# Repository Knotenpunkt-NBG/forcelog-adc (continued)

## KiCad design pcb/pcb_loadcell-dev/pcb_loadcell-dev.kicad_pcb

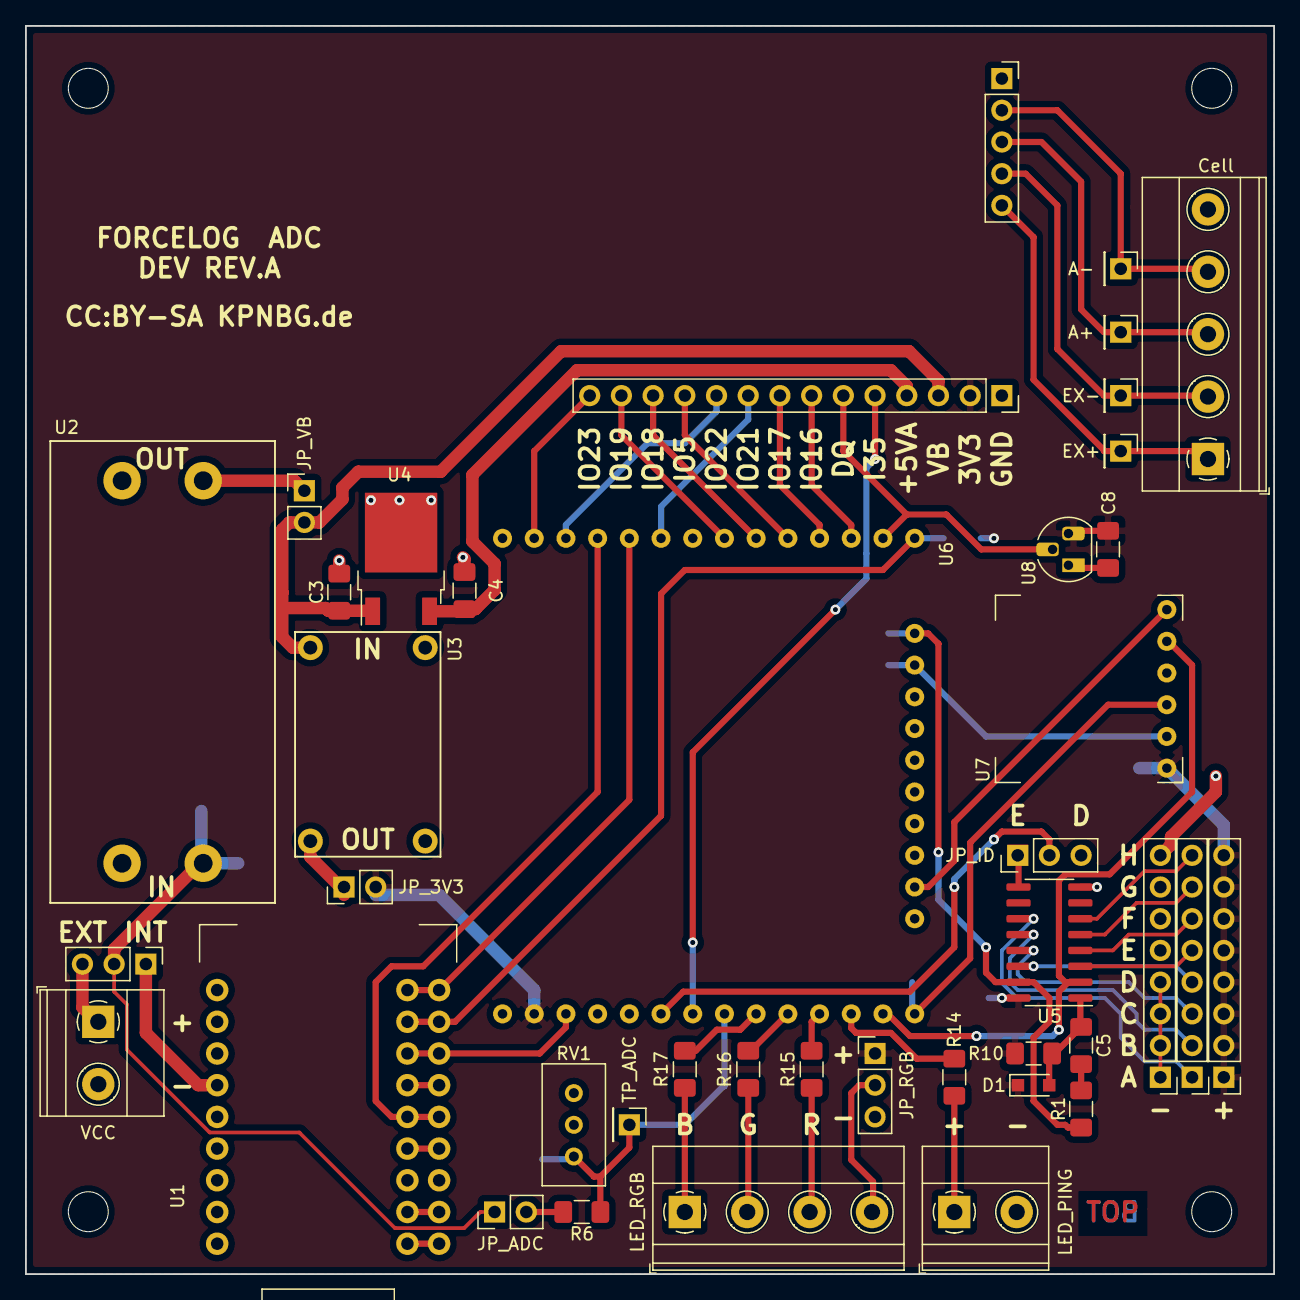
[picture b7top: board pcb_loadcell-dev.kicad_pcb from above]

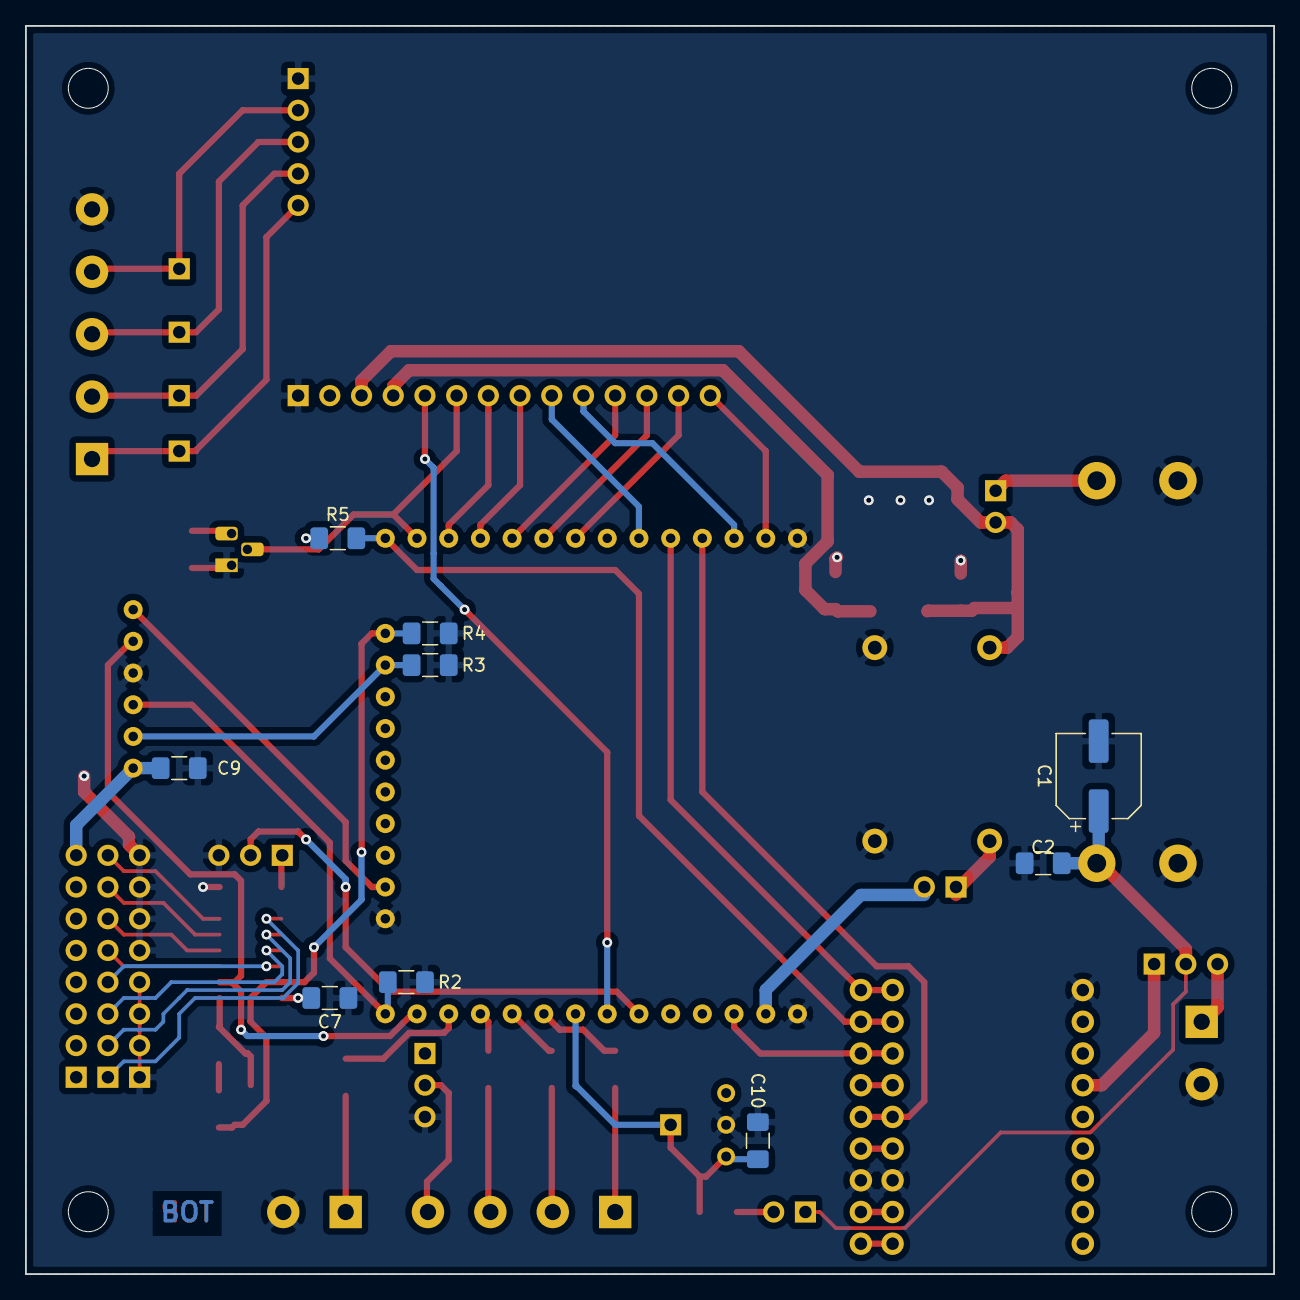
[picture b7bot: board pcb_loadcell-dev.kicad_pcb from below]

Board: 2 copper layers, 100.0 x 100.0 mm, 54 parts (9 on the bottom side), 55 nets.

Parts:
C1: 10µ; CP_Elec_6.3x4.9
C2, C4, C5, C7, C8, C9, C10: 100n; C_1206_3216Metric_Pad1.42x1.75mm_HandSolder
C3: 330n; C_1206_3216Metric_Pad1.42x1.75mm_HandSolder
D1: BAT54; D_SOD-323_HandSoldering
JP1: JUMPER3; PinHeader_1x03_P2.54mm_Vertical
JP2: JP_3V3; PinHeader_1x02_P2.54mm_Vertical
JP3: JP_ID; PinHeader_1x03_P2.54mm_Vertical
JP4: JP_VB; PinHeader_1x02_P2.54mm_Vertical
JP6: JP_ADC; PinHeader_1x02_P2.54mm_Vertical
JP8: JP_RGB; PinHeader_1x03_P2.54mm_Vertical
P1: VCC; TerminalBlock_Phoenix_MKDS-1,5-2_1x02_P5.00mm_Horizontal
P2, P3, P4: CONN_01X08; PinHeader_1x08_P2.54mm_Vertical
P5: CONN_01X14; PinSocket_1x14_P2.54mm_Vertical
P6, P7, P9, P15: CONN_01X01; MountingHole_3.2mm_M3
P8: TP_ADC; PinHeader_1x01_P2.54mm_Vertical
P10: LED_PING; TerminalBlock_Phoenix_MKDS-1,5-2_1x02_P5.00mm_Horizontal
P11: LED_RGB; TerminalBlock_Phoenix_MKDS-1,5-4_1x04_P5.00mm_Horizontal
P12: A-; PinHeader_1x01_P2.54mm_Vertical
P13: A+; PinHeader_1x01_P2.54mm_Vertical
P14: Cell; TerminalBlock_Phoenix_MKDS-1,5-5_1x05_P5.00mm_Horizontal
P16: CONN_01X05; PinSocket_1x05_P2.54mm_Vertical
P17: EX-; PinHeader_1x01_P2.54mm_Vertical
P18: EX+; PinHeader_1x01_P2.54mm_Vertical
R1, R10: 470; R_1206_3216Metric_Pad1.42x1.75mm_HandSolder
R2, R3, R4, R5: 10k; R_1206_3216Metric_Pad1.42x1.75mm_HandSolder
R6: 1k; R_1206_3216Metric_Pad1.42x1.75mm_HandSolder
R14, R17: 22; R_1206_3216Metric_Pad1.42x1.75mm_HandSolder
R15: 120; R_1206_3216Metric_Pad1.42x1.75mm_HandSolder
R16: 86; R_1206_3216Metric_Pad1.42x1.75mm_HandSolder
RV1: 1k; Potentiometer_Bourns_3296W_Vertical
U1: FT232breakout; ft232rl_breakout_combined
U2: BoostConverter; MT3608_module_boost
U3: BuckConverter; dsn-mini-360_buck
U4: 7805; TO-252-2
U5: 74HC165; SOIC-16_3.9x9.9mm_P1.27mm
U6: ESP32-WROOM-32U; ESP32-WROOM-BREAKOUT
U7: W25Q128; W25Q128-module
U8: DS18B20; TO-92_HandSolder

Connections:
+3V3: C7.1, C8.1, C9.1, D1.K, JP2.2, JP8.1, P2.1, P2.2, P2.3, P2.4, P2.5, P2.6, P2.7, P2.8, P5.2, R5.2, R10.1, U5.16, U6.2, U7.1, U8.3
+5VA: C4.1, P5.4, U4.3
/Digital/BLUE: R17.1, U6.9
/Digital/DQ: P5.6, U6.26, U8.2
/Digital/DTR: R5.1, U1.8, U6.25
/Digital/GREEN: R16.1, U6.10
/Digital/HCLK: U5.2, U6.13, U7.5
/Digital/HMISO: R2.1, U6.14, U7.3
/Digital/HMOSI: U6.16, U7.6
/Digital/H~CS: R3.1, U6.23, U7.2
/Digital/I35: P5.5, U6.7
/Digital/IO_5|V~CS: P5.11, U6.29
/Digital/IO_16: P5.7, U6.27
/Digital/IO_17: P5.8, U6.28
/Digital/IO_18|VCLK: P5.12, U6.30
/Digital/IO_19|VMISO: P5.13, U6.31
/Digital/IO_21|SDA: P5.9, U6.33
/Digital/IO_22|SCL: P5.10, U6.36
/Digital/IO_23|VMOSI: P5.14, U6.37
/Digital/PING: R14.2, U6.12
/Digital/QH: JP3.2, U6.6
/Digital/RED: R15.1, U6.11
/Digital/RTS: U1.7, U6.3
/Digital/RXD: U1.9, U6.34
/Digital/SH: R1.1, R4.2, U5.15, U6.24
/Digital/TXD: U1.5, U6.35
GND: C1.2, C2.2, C3.2, C4.2, C7.2, C8.2, C9.2, C10.2, JP3.3, JP8.3, P1.2, P3.1, P3.2, P3.3, P3.4, P3.5, P3.6, P3.7, P3.8, P5.1, P10.2, P14.5, P16.1, R2.2, R3.2, R4.1, RV1.2, U1.3, U1.18, U2.1, U2.4, U3.2, U3.4, U4.2, U5.8, U6.1, U6.15, U6.38, U7.4, U8.1
unnamed: C5.1, D1.A, R10.2, U5.1
unnamed: C5.2, R1.2
unnamed: C10.1, P8.1, R6.1, RV1.1, U6.8
unnamed: JP1.1, U1.15
unnamed: JP1.3, P1.1
unnamed: JP2.1, U3.3
unnamed: JP3.1, U5.9
unnamed: JP4.1, U2.3
unnamed: JP6.2, R6.2
unnamed: JP8.2, P11.4
unnamed: P4.1, U5.11
unnamed: P4.2, U5.12
unnamed: P4.3, U5.13
unnamed: P4.4, U5.14
unnamed: P4.5, U5.3
unnamed: P4.6, U5.4
unnamed: P4.7, U5.5
unnamed: P4.8, U5.6
unnamed: P10.1, R14.1
unnamed: P11.1, R17.2
unnamed: P11.2, R16.2
unnamed: P11.3, R15.2
unnamed: P12.1, P14.4, P16.2
unnamed: P13.1, P14.3, P16.3
unnamed: P14.1, P16.5, P18.1
unnamed: P14.2, P16.4, P17.1
VCC: C1.1, C2.1, JP1.2, JP6.1, U2.2
Vboost: C3.1, JP4.2, P5.3, U3.1, U4.1

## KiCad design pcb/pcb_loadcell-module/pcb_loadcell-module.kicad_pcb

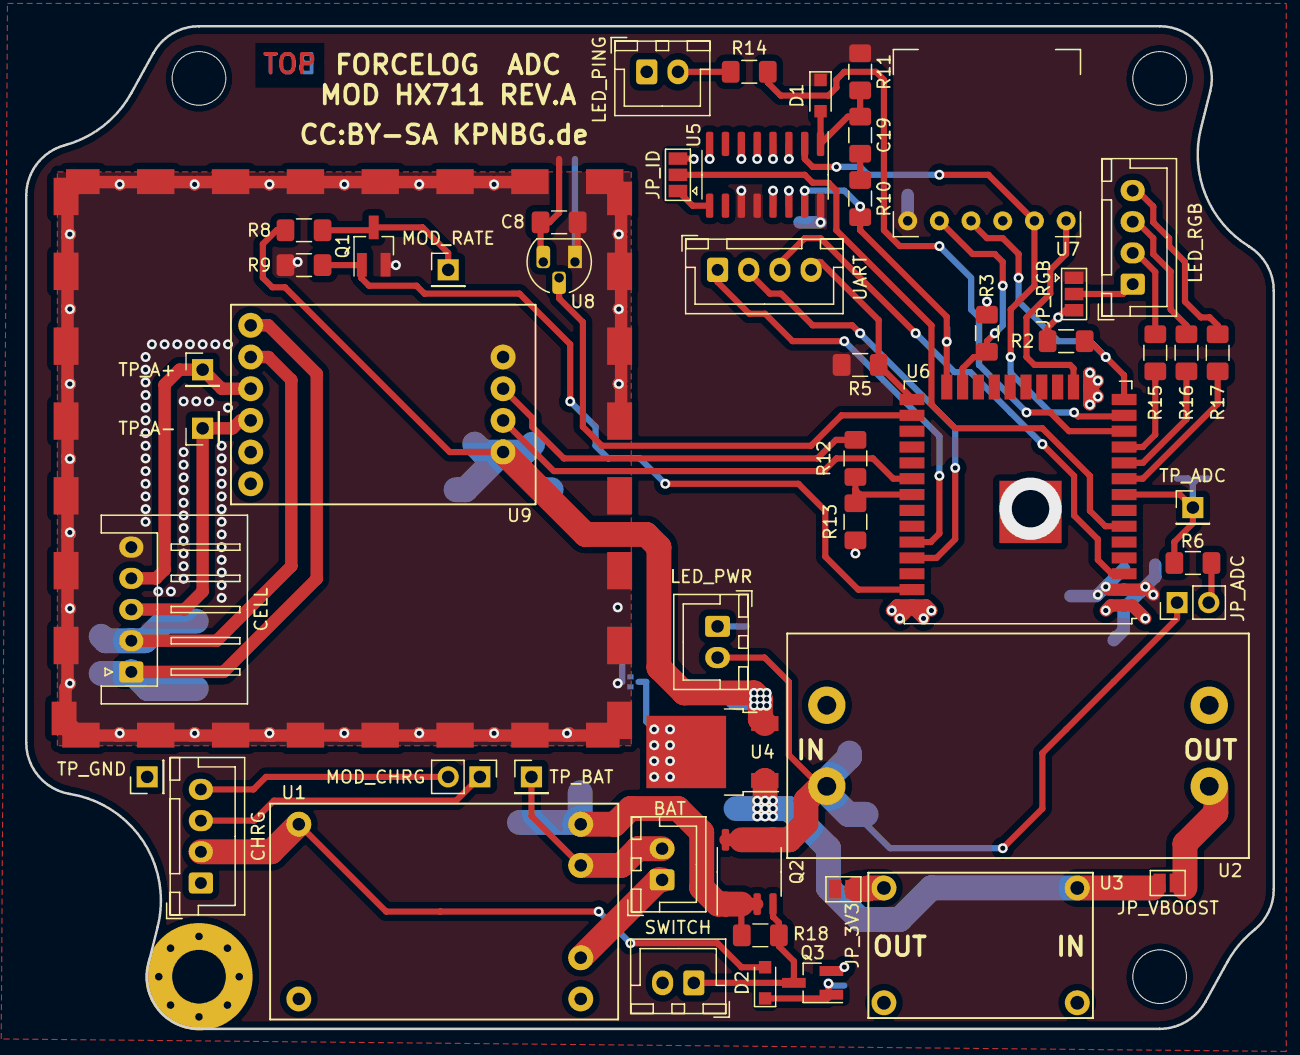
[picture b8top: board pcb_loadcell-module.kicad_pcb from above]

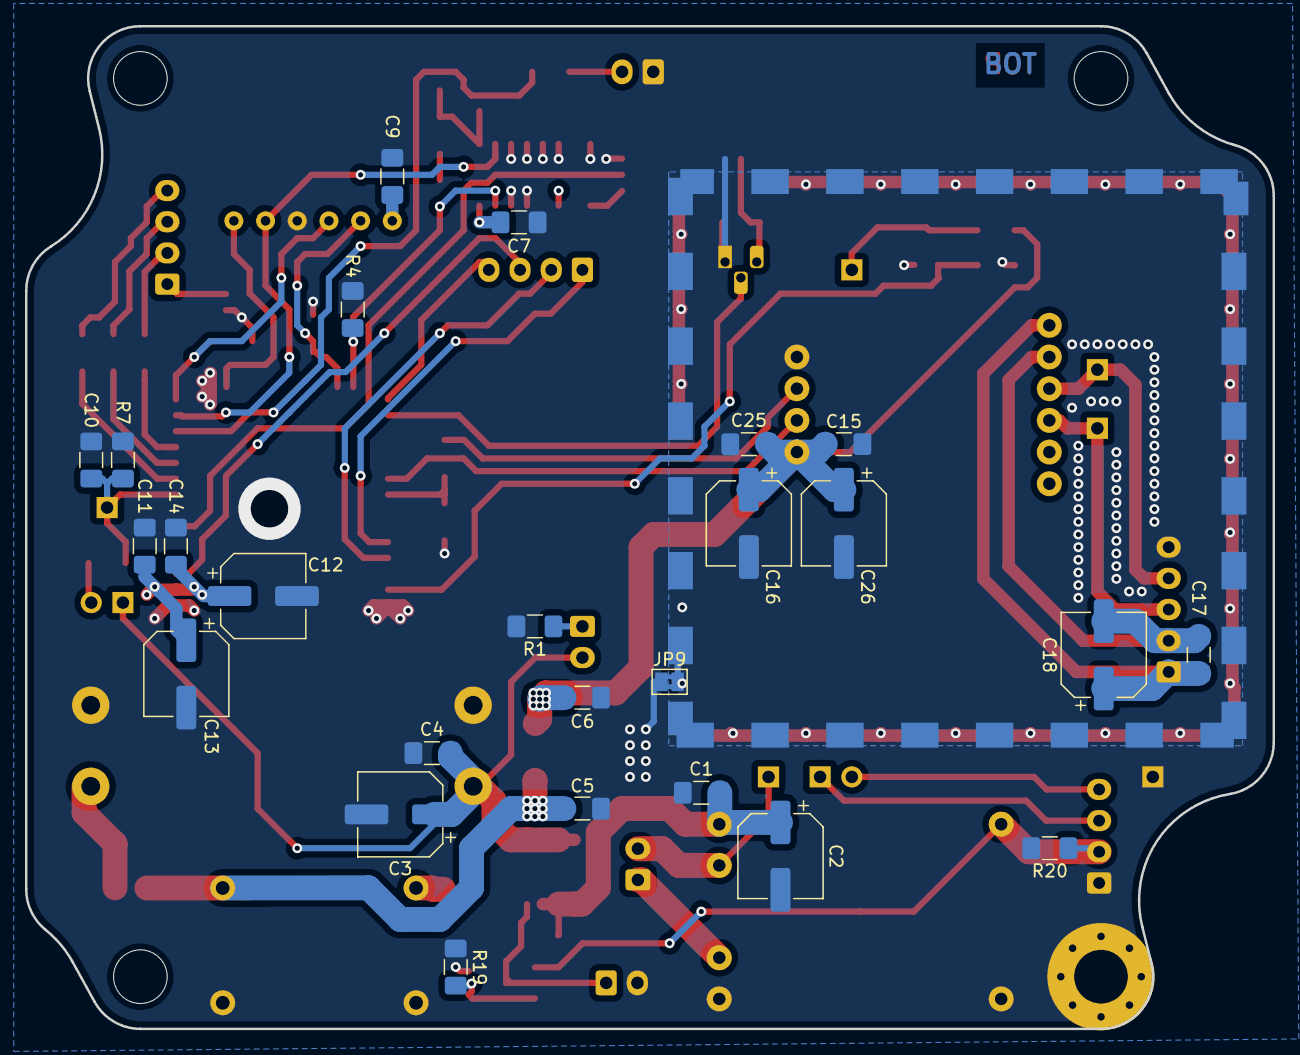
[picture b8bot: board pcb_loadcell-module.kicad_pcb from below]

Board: 2 copper layers, 100.0 x 80.4 mm, 82 parts (26 on the bottom side), 50 nets.

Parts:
C1, C4, C6, C7, C8, C9, C10, C11, C14, C15, C17, C19, C25: 100n; C_1206_3216Metric_Pad1.42x1.75mm_HandSolder
C2, C3, C12, C13, C16, C18, C26: 10µ; CP_Elec_6.3x5.7
C5: 330n; C_1206_3216Metric_Pad1.42x1.75mm_HandSolder
D1: BAT54; D_SOD-323_HandSoldering
D2: 1n4148; D_SOD-323_HandSoldering
JP1: JP_VBOOST; SolderJumper-2_P1.3mm_Open_Pad1.0x1.5mm
JP2: JP_3V3; SolderJumper-2_P1.3mm_Open_Pad1.0x1.5mm
JP3: JP_ID; SolderJumper-3_P1.3mm_Open_Pad1.0x1.5mm
JP6: JP_ADC; PinHeader_1x02_P2.54mm_Vertical
JP8: JP_RGB; SolderJumper-3_P1.3mm_Open_Pad1.0x1.5mm
JP9: Jumper_2_Bridged; SolderJumper-2_P1.3mm_Bridged2Bar_Pad1.0x1.5mm
P1: TP_GND; PinHeader_1x01_P2.54mm_Vertical
P2: BAT; JST_XH_B2B-XH-A_1x02_P2.50mm_Vertical
P3: TP_BAT; PinHeader_1x01_P2.54mm_Vertical
P4: CHRG; JST_XH_B4B-XH-A_1x04_P2.50mm_Vertical
P5: MOD_CHRG; PinHeader_1x02_P2.54mm_Vertical
P6: SWITCH; JST_XH_B2B-XH-A_1x02_P2.50mm_Vertical
P7: LED_PWR; JST_XH_B2B-XH-A_1x02_P2.50mm_Vertical
P8: TP_ADC; PinHeader_1x01_P2.54mm_Vertical
P9: UART; JST_XH_B4B-XH-A_1x04_P2.50mm_Vertical
P10: LED_PING; JST_XH_B2B-XH-A_1x02_P2.50mm_Vertical
P11: LED_RGB; JST_XH_B4B-XH-A_1x04_P2.50mm_Vertical
P12: CELL; JST_XH_S5B-XH-A_1x05_P2.50mm_Horizontal
P13: TP_A+; PinHeader_1x01_P2.54mm_Vertical
P14: TP_A-; PinHeader_1x01_P2.54mm_Vertical
P15, P16: SHIELD; Shield_TE2118726-2
P17: MNT_ins; MountingHole_4.3mm_M4_Pad_Via
P18, P19: MNT_ins; MountingHole_4.3mm_M4_DIN965
P20: MNT_shield; MountingHole_4.3mm_M4_DIN965
P21: MOD_RATE; PinHeader_1x01_P2.54mm_Vertical
Q1, Q3: 2N7002; SOT-23_Handsoldering
Q2: Si4403DDY; SO-8_3.9x4.9mm_P1.27mm
R1: 270; R_1206_3216Metric_Pad1.42x1.75mm_HandSolder
R2, R3, R4, R5, R8, R9, R11, R18, R19, R20: 10k; R_1206_3216Metric_Pad1.42x1.75mm_HandSolder
R6: 750; R_1206_3216Metric_Pad1.42x1.75mm_HandSolder
R7: 1k5; R_1206_3216Metric_Pad1.42x1.75mm_HandSolder
R10, R12: 470; R_1206_3216Metric_Pad1.42x1.75mm_HandSolder
R13: 910; R_1206_3216Metric_Pad1.42x1.75mm_HandSolder
R14, R17: 22; R_1206_3216Metric_Pad1.42x1.75mm_HandSolder
R15: 120; R_1206_3216Metric_Pad1.42x1.75mm_HandSolder
R16: 91; R_1206_3216Metric_Pad1.42x1.75mm_HandSolder
U1: TP4056withprotect; TP4056_module_prot
U2: BoostConverter; MT3608_module_boost
U3: BuckConverter; dsn-mini-360_buck
U4: 7805; TO-252-2
U5: 74HC165; SOIC-16_3.9x9.9mm_P1.27mm
U6: ESP32-WROOM-32U
U7: W25Q128; W25Q128-module
U8: DS18B20; TO-92_HandSolder
U9: HX711; hx711

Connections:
+3V3: C7.1, C8.1, C9.1, C11.1, C12.1, C13.1, C14.1, D1.K, JP2.2, JP8.1, R5.2, R11.1, U5.11, U5.12, U5.16, U6.2, U7.1, U8.3
+5V: C6.1, C15.1, C16.1, C25.1, C26.1, R8.1, U4.3, U9.7
+BATT: C3.1, C4.1, JP6.1, P7.2, Q2.5, Q2.6, Q2.7, Q2.8, U2.2
/Analog/DT: R12.2, U9.9
/Analog/EX+: C17.1, C18.1, P12.1, U9.1
/Analog/EX-: C17.2, C18.2, P12.2, U9.2
/Analog/RATE: Q1.1, R9.2, U6.37
/Analog/SCK: U6.30, U9.8
/Digital/BLUE: R17.1, U6.9
/Digital/DQ: U6.26, U8.2
/Digital/DTR: P9.4, R5.1, U6.25
/Digital/GREEN: R16.1, U6.10
/Digital/HCLK: U5.2, U6.13, U7.5
/Digital/HMISO: R2.1, U6.14, U7.3
/Digital/HMOSI: U6.16, U7.6
/Digital/H~CS: R3.1, U6.23, U7.2
/Digital/PING: R14.2, U6.12
/Digital/QH: JP3.2, U6.6
/Digital/RED: R15.1, U6.11
/Digital/RTS: P9.3, U6.3
/Digital/RXD: P9.1, U6.34
/Digital/SH: R4.2, R10.1, U5.15, U6.24
/Digital/TXD: P9.2, U6.35
/Digital/VMISO: R12.1, R13.2, U6.31
/VBOOST: C5.1, JP1.2, U3.1, U4.1
GND: C1.2, C2.2, C3.2, C4.2, C5.2, C6.2, C7.2, C8.2, C9.2, C10.2, C11.2, C12.2, C13.2, C14.2, C15.2, C16.2, C25.2, C26.2, JP3.3, JP8.3, JP9.1, JP9.2, P1.1, P4.1, P6.2, P10.1, P12.5, P15.1, P16.1, P17.1, Q1.2, Q3.2, R1.2, R2.2, R3.2, R4.1, R7.1, R9.1, R13.1, R19.2, R20.2, U1.2, U1.3, U2.1, U2.4, U3.2, U3.4, U4.2, U5.3, U5.4, U5.5, U5.6, U5.8, U5.13, U5.14, U6.1, U6.15, U6.38, U6.39, U7.4, U8.1, U9.10
unnamed: C1.1, C2.1, Q2.1, Q2.2, Q2.3, R18.1, U1.6
unnamed: C10.1, P8.1, R6.1, R7.2, U6.8
unnamed: C19.1, D1.A, R11.2, U5.1
unnamed: C19.2, R10.2
unnamed: D2.A, P4.2, R20.1, U1.1
unnamed: D2.K, Q3.1, R19.1
unnamed: JP1.1, U2.3
unnamed: JP2.1, U3.3
unnamed: JP3.1, U5.9
unnamed: JP6.2, R6.2
unnamed: JP8.2, P11.1
unnamed: P2.1, U1.4
unnamed: P2.2, P3.1, U1.5
unnamed: P4.3, P5.1
unnamed: P4.4, P5.2
unnamed: P6.1, Q2.4, Q3.3, R18.2
unnamed: P7.1, R1.1
unnamed: P10.2, R14.1
unnamed: P11.2, R15.2
unnamed: P11.3, R16.2
unnamed: P11.4, R17.2
unnamed: P12.3, P14.1, U9.4
unnamed: P12.4, P13.1, U9.3
unnamed: P21.1, Q1.3, R8.2

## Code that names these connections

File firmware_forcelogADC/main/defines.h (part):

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

//Temperature internal
#define OWB_GPIO				4
#define GPIO_OWB_SENSE			34		//GPIO for the OneWire Sense input. Enables automatic detection of new sensor
#define MAX_DEVICES          	(8)
#define TEMP_INTERNAL_PERIOD	30		// period of temperature measurements in seconds. must be higher then 2s
#define MAX_TEMP				50.0	//Max temperature (°C)for the adc to operate in. if this is crossed the adc shuts down all functions
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#define TAG_RGB		"RGB"
#define TAG_WIFI	"WiFi"
#define TAG_CONF	"CONFIG"
#define TAG_BATMON	"BATMON"
#define TAG_TEMPINT	"TEMPINT"
#define TAG_REDUND	"REDUND"
#define TAG_STORAGE "STORAGE"
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
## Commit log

2020-10-06 Update
    -renamed uart to serial
    -fixed wifi
2020-10-26 Coded again
    -added 1-wire component and support for internal temperature probe
    -added support for sd card for backup storage if connection is lost
    -refactored config so both interfaces (tcp and uart) can accept the same cmdlets
    -added battery voltage sensing
2020-11-03 Coded again
    -changed event groups to direct to task notifications for speed
    -added SD-card support for config files
    -reworked the flow of the running tasks so the code looks cleaner
2020-11-03 removed cad
2020-11-23 Cleaned up Config
    -added init routine
    -fixed bug between comm and config
    -added granular storage
2020-11-24 Interlude
    -started better Task synchronisation
    -changed init routine from filepaths to struct
    -changed wifi config to allow access point and station
2021-02-28 motherboard dev rev.c
2021-03-06 ADC Component
    put adc routines into components
2022-08-03 CleanUp
2023-01-01 Update esp-idf
    Updated the idf and routines for idf v5.0
2023-01-02 PCB MB_DEV update 1.1
    +Added a jumper for GPIO12 for flashing and setting efuse for 3.3 Flash operation
    +Added Text Variables to Schematic and PCB
    +introduced versioning of pcb
    +added filenames and version to schematic sheets
2023-01-02 PCB MB-DEV update
    +Added a jumper for GPIO12 for flashing and setting efuse for 3.3 Flash operation
    +Added Text Variables to Schematic and PCB
    +introduced versioning of pcb
    +added filenames and version to schematic sheets
